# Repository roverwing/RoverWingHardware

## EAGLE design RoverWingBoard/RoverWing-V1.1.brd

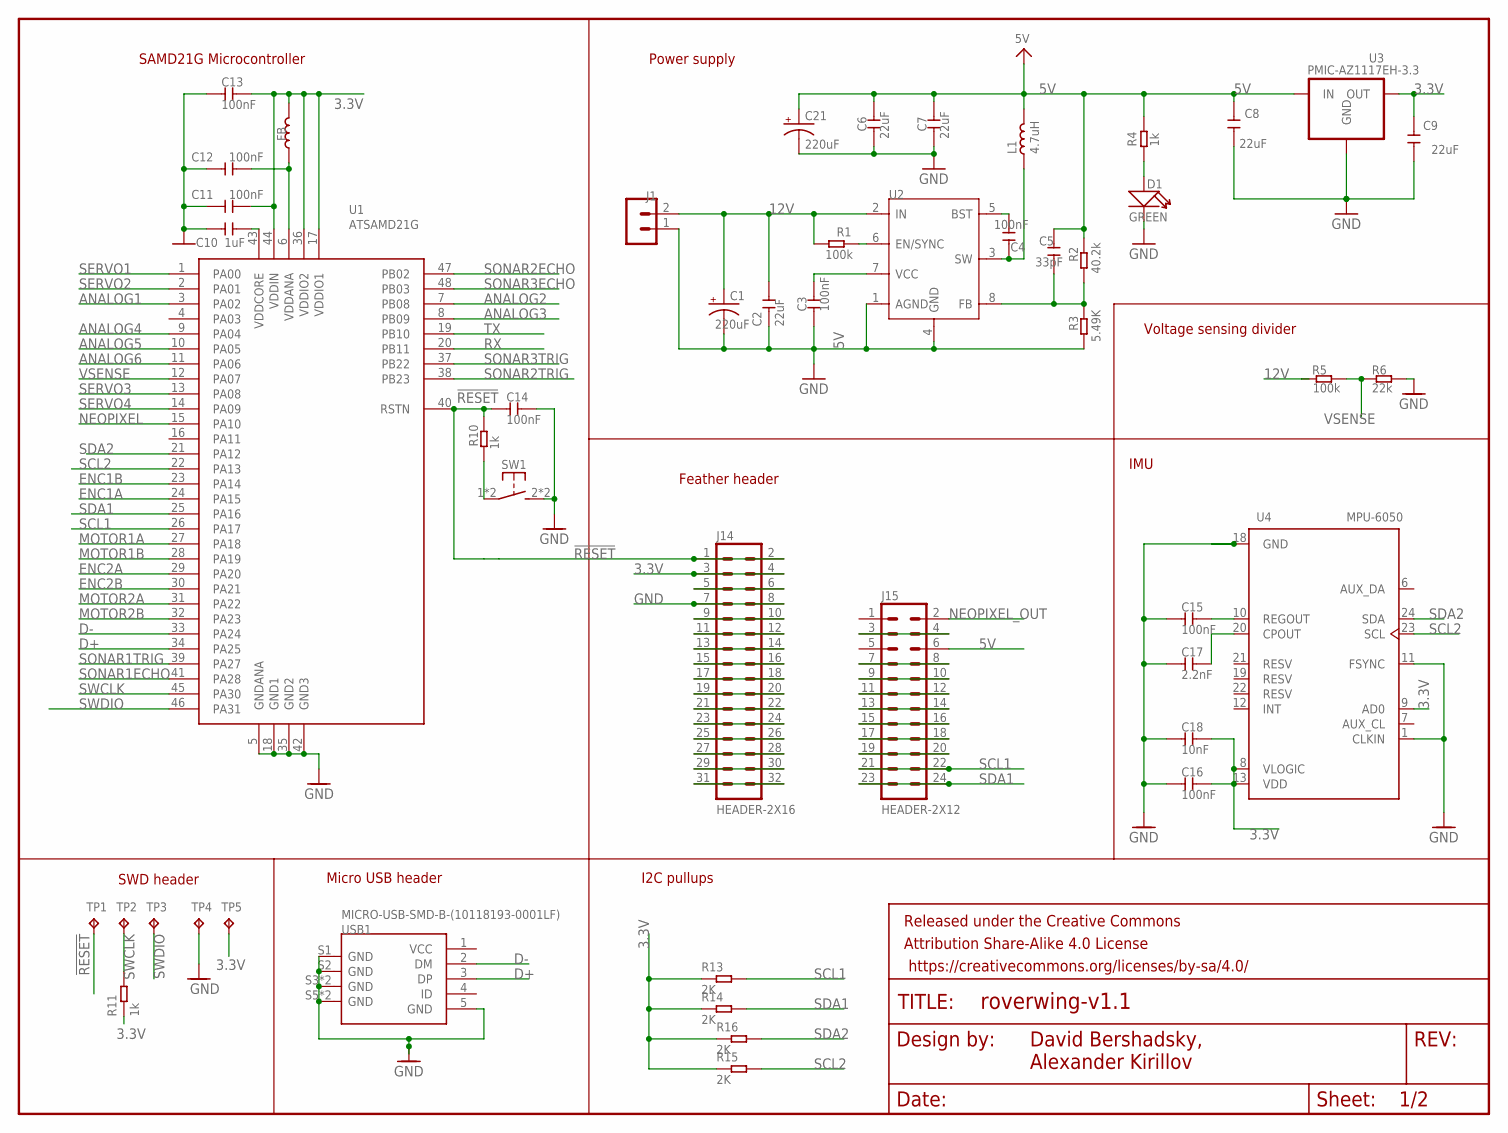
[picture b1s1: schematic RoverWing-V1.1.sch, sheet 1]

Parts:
C1: 220uF; CAP-8X10.5
C2, C6, C7, C8, C9: 22uF; 0805
C3, C4, C11, C12, C13, C14, C15, C16: 100nF; 0805
C5: 33pF; 0805
C10: 1uF; 0805
C17: 2.2nF; 0805
C18: 10nF; 0805
C21: 220uF; CAP-6.3X5.4
D1: GREEN; LED-0805
FB: 330R-1500MA; 0805
FRAME2: FRAME-LETTERNO_PACKAGE; DUMMY
J1: HEADER-VH; B2P-VH
J14: HEADER-2X16; 2X16
J15: HEADER-2X12; 2X12
L1: 4.7uH; IND_TDK_7.1X6.5
R1, R5: 100k; 0805
R2: 40.2k; 0805
R3: 5.49K; 0805
R4, R10, R11: 1k; 0805
R6: 22k; 0805
R13, R14, R15, R16: 2K; R0603
SW1: SW-TACTILE-4.5X4.5_SMD; TL3305
TP1, TP2, TP3, TP4, TP5: TPTP15R; TP15R
U1: ATSAMD21G; TQFP-48-EDITED
U2: MP2225; SOT-23-8
U3: PMIC-AZ1117EH-3.3; SOT223
U4: MPU-6050; QFN50P400X400X95-24N
USB1: MICRO-USB-SMD-B-(10118193-0001LF); MICRO-USB5+6P-SMD-0.65-B

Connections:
3.3V: C9.2, C11.2, C13.2, C16.2, C18.2, FB.2, J14.3, J14.4, R11.1, R13.1, R14.1, R15.1, R16.1, TP5.TP, U1.17 (VDDIO1), U1.36 (VDDIO2), U1.44 (VDDIN), U3.2 (OUT), U3.4 (OUT), U4.8 (VLOGIC), U4.9 (AD0), U4.13 (VDD); also elsewhere on the board
5V: C5.2, C6.2, C7.2, C8.2, C21.+, J15.6, L1.2, R2.1, R4.2, U3.3 (IN); also elsewhere on the board
12V: C1.+, C2.2, J1.2, R1.2, R5.2, U2.2 (IN); also elsewhere on the board
!RESET: C14.1, J14.1, J14.2, R10.2, TP1.TP, U1.40 (RSTN)
ANALOG1: U1.3 (PA02); also elsewhere on the board
ANALOG2: U1.7 (PB08); also elsewhere on the board
ANALOG3: U1.8 (PB09); also elsewhere on the board
ANALOG4: U1.9 (PA04); also elsewhere on the board
ANALOG5: U1.10 (PA05); also elsewhere on the board
ANALOG6: U1.11 (PA06); also elsewhere on the board
BST: C4.1, U2.5 (BST)
D+: U1.34 (PA25), USB1.3 (DP)
D-: U1.33 (PA24), USB1.2 (DM)
ENC1A: U1.24 (PA15); also elsewhere on the board
ENC1B: U1.23 (PA14); also elsewhere on the board
ENC2A: U1.29 (PA20); also elsewhere on the board
ENC2B: U1.30 (PA21); also elsewhere on the board
FB: C5.1, R2.2, R3.1, U2.8 (FB)
GND: C1.-, C2.1, C3.1, C6.1, C7.1, C8.1, C9.1, C10.1, C11.1, C12.1, C13.1, C14.2, C15.1, C16.1, C17.1, C18.1, C21.-, D1.-, J1.1, J14.7, J14.8, R3.2, R6.2, SW1.2 (S1), SW1.3 (S1), TP4.TP, U1.5 (GNDANA), U1.18 (GND1), U1.35 (GND2), U1.42 (GND3), U2.1 (AGND), U2.4 (GND), U3.1 (GND), U4.1 (CLKIN), U4.11 (FSYNC), U4.18 (GND), USB1.5 (GND), USB1.S1 (GND), USB1.S2 (GND), USB1.S3 (GND), USB1.S4 (GND), USB1.S5 (GND), USB1.S6 (GND); also elsewhere on the board
MOTOR1A: U1.27 (PA18); also elsewhere on the board
MOTOR1B: U1.28 (PA19); also elsewhere on the board
MOTOR2A: U1.31 (PA22); also elsewhere on the board
MOTOR2B: U1.32 (PA23); also elsewhere on the board
unnamed: C17.2, U4.20 (CPOUT)
unnamed: J15.3, J15.4
unnamed: C15.2, U4.10 (REGOUT)
unnamed: J15.7, J15.8
unnamed: R10.1, SW1.1, SW1.4 (P1)
unnamed: J15.9, J15.10
unnamed: C10.2, U1.43 (VDDCORE)
unnamed: J15.11, J15.12
unnamed: D1.+, R4.1
unnamed: J15.15, J15.16
unnamed: J15.13, J15.14
unnamed: R1.1, U2.6 (EN/SYNC)
unnamed: C3.2, U2.7 (VCC)
unnamed: J14.5, J14.6
unnamed: J15.17, J15.18
unnamed: J15.19, J15.20
unnamed: J14.9, J14.10
unnamed: J14.11, J14.12
unnamed: J14.13, J14.14
unnamed: J14.15, J14.16
unnamed: J14.17, J14.18
unnamed: J14.19, J14.20
unnamed: J14.21, J14.22
unnamed: J14.23, J14.24
unnamed: J14.25, J14.26
unnamed: J14.27, J14.28
unnamed: J14.29, J14.30
unnamed: J14.31, J14.32
NEOPIXEL: U1.15 (PA10); also elsewhere on the board
NEOPIXEL_OUT: J15.2; also elsewhere on the board
RX: U1.20 (PB11); also elsewhere on the board
SCL1: J15.21, J15.22, R13.2, U1.26 (PA17); also elsewhere on the board
SCL2: R15.2, U1.22 (PA13), U4.23 (SCL); also elsewhere on the board
SDA1: J15.23, J15.24, R14.2, U1.25 (PA16); also elsewhere on the board
SDA2: R16.2, U1.21 (PA12), U4.24 (SDA); also elsewhere on the board
SERVO1: U1.1 (PA00); also elsewhere on the board
SERVO2: U1.2 (PA01); also elsewhere on the board
SERVO3: U1.13 (PA08); also elsewhere on the board
SERVO4: U1.14 (PA09); also elsewhere on the board
SONAR1ECHO: U1.41 (PA28); also elsewhere on the board
SONAR1TRIG: U1.39 (PA27); also elsewhere on the board
SONAR2ECHO: U1.47 (PB02); also elsewhere on the board
SONAR2TRIG: U1.38 (PB23); also elsewhere on the board
SONAR3ECHO: U1.48 (PB03); also elsewhere on the board
SONAR3TRIG: U1.37 (PB22); also elsewhere on the board
SW: C4.2, L1.1, U2.3 (SW)
SWCLK: R11.2, TP2.TP, U1.45 (PA30)
SWDIO: TP3.TP, U1.46 (PA31)
TX: U1.19 (PB10); also elsewhere on the board
VDDANA: C12.2, FB.1, U1.6 (VDDANA)
VSENSE: R5.1, R6.1, U1.12 (PA07)

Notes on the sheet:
SWD header
David Bershadsky, Alexander Kirillov
SAMD21G Microcontroller
Micro USB header
Power supply
Feather header
IMU
Voltage sensing divider
I2C pullups

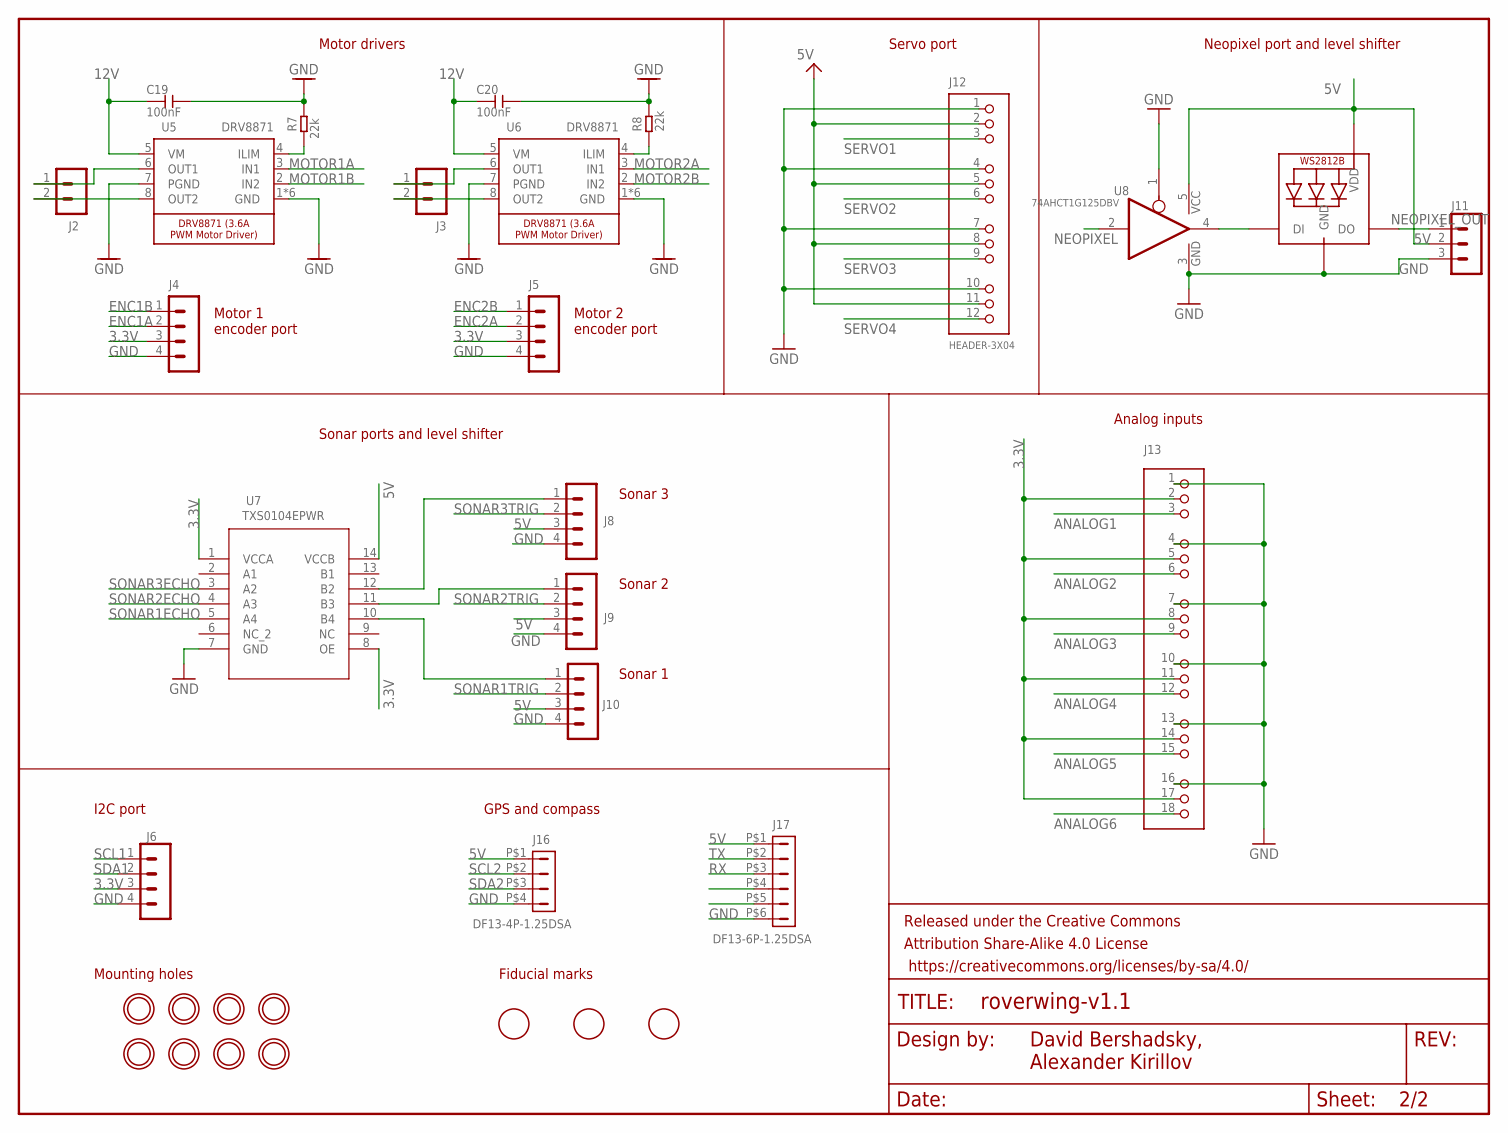
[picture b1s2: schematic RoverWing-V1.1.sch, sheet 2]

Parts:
C19, C20: 100nF; 0805
D2: WS2812B3535; LED3535
FRAME1: FRAME-LETTERNO_PACKAGE; DUMMY
J2, J3: HEADER-VH; B2P-VH
J4, J5, J6, J8, J9, J10: HEADER-PH-4P; B4B-PH-K
J11: HEADER-PH-3P; B3B-PH-K
J12: HEADER-3X04; 3X04
J13: HEADER-3X06"; 3X06
J16: DF13-4P-1.25DSA
J17: DF13-6P-1.25DSA
R7, R8: 22k; 0805
U5, U6: DRV8871; HSOP8
U7: TXS0104EPWR; PW14
U8: 74AHCT1G125DBV; SOT23-5
U$3, U$4, U$14, U$15, U$24, U$25, U$26, U$27: MOUNTINGHOLE3.0_NPH; MOUNTINGHOLE_3.0_NPH
U$11, U$13, U$17: FIDUCIAL; FIDUCIAL_1MM

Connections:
3.3V: J4.3, J5.3, J6.3, J13.2, J13.5, J13.8, J13.11, J13.14, J13.17, U7.1 (VCCA), U7.8 (OE); also elsewhere on the board
5V: D2.3 (VDD), J8.3, J9.3, J10.3, J11.2, J12.2, J12.5, J12.8, J12.11, J16.P$1 (1), J17.P$1 (1), U7.14 (VCCB), U8.5 (VCC); also elsewhere on the board
12V: C19.1, C20.1, U5.5 (VM), U6.5 (VM); also elsewhere on the board
ANALOG1: J13.3; also elsewhere on the board
ANALOG2: J13.6; also elsewhere on the board
ANALOG3: J13.9; also elsewhere on the board
ANALOG4: J13.12; also elsewhere on the board
ANALOG5: J13.15; also elsewhere on the board
ANALOG6: J13.18; also elsewhere on the board
ENC1A: J4.2; also elsewhere on the board
ENC1B: J4.1; also elsewhere on the board
ENC2A: J5.2; also elsewhere on the board
ENC2B: J5.1; also elsewhere on the board
GND: C19.2, C20.2, D2.1 (GND), J4.4, J5.4, J6.4, J8.4, J9.4, J10.4, J11.3, J12.1, J12.4, J12.7, J12.10, J13.1, J13.4, J13.7, J13.10, J13.13, J13.16, J16.P$4 (4), J17.P$6 (6), R7.2, R8.2, U5.1 (GND), U5.7 (PGND), U5.GND, U5.P$1 (GND), U5.P$2 (GND), U5.P$3 (GND), U5.P$4 (GND), U6.1 (GND), U6.7 (PGND), U6.GND, U6.P$1 (GND), U6.P$2 (GND), U6.P$3 (GND), U6.P$4 (GND), U7.7 (GND), U8.1 (OE), U8.3 (GND); also elsewhere on the board
MOTOR1A: U5.3 (IN1); also elsewhere on the board
MOTOR1B: U5.2 (IN2); also elsewhere on the board
MOTOR2A: U6.3 (IN1); also elsewhere on the board
MOTOR2B: U6.2 (IN2); also elsewhere on the board
unnamed: J3.2, U6.8 (OUT2)
unnamed: J3.1, U6.6 (OUT1)
unnamed: J2.2, U5.8 (OUT2)
unnamed: J10.1, U7.10 (B4)
unnamed: J8.1, U7.12 (B2)
unnamed: J2.1, U5.6 (OUT1)
unnamed: R7.1, U5.4 (ILIM)
unnamed: R8.1, U6.4 (ILIM)
unnamed: J9.1, U7.11 (B3)
unnamed: D2.2 (DI), U8.4 (O)
NEOPIXEL: U8.2 (I); also elsewhere on the board
NEOPIXEL_OUT: D2.4 (DO), J11.1; also elsewhere on the board
RX: J17.P$3 (3); also elsewhere on the board
SCL1: J6.1; also elsewhere on the board
SCL2: J16.P$2 (2); also elsewhere on the board
SDA1: J6.2; also elsewhere on the board
SDA2: J16.P$3 (3); also elsewhere on the board
SERVO1: J12.3; also elsewhere on the board
SERVO2: J12.6; also elsewhere on the board
SERVO3: J12.9; also elsewhere on the board
SERVO4: J12.12; also elsewhere on the board
SONAR1ECHO: U7.5 (A4); also elsewhere on the board
SONAR1TRIG: J10.2; also elsewhere on the board
SONAR2ECHO: U7.4 (A3); also elsewhere on the board
SONAR2TRIG: J9.2; also elsewhere on the board
SONAR3ECHO: U7.3 (A2); also elsewhere on the board
SONAR3TRIG: J8.2; also elsewhere on the board
TX: J17.P$2 (2); also elsewhere on the board

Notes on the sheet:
Motor drivers
Motor 2 encoder port
Motor 1 encoder port
Sonar ports and level shifter
Analog inputs
Neopixel port and level shifter
Servo port
Sonar 3
Sonar 2
Sonar 1
Mounting holes
Fiducial marks
I2C port
GPS and compass
David Bershadsky, Alexander Kirillov

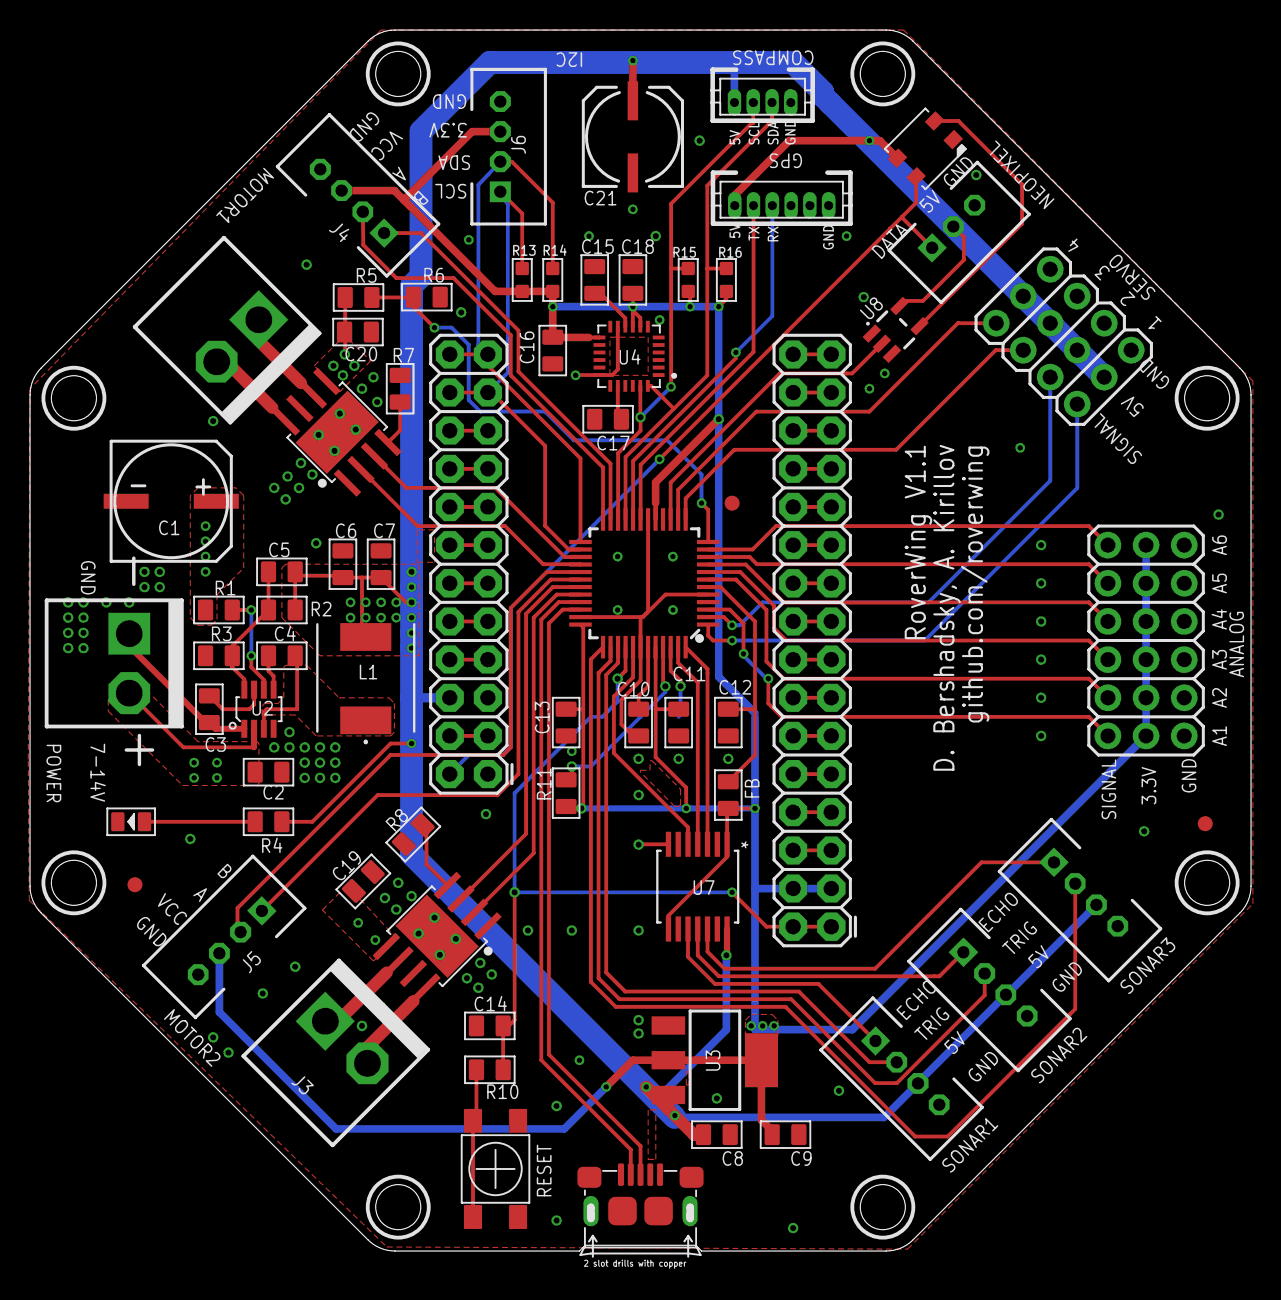
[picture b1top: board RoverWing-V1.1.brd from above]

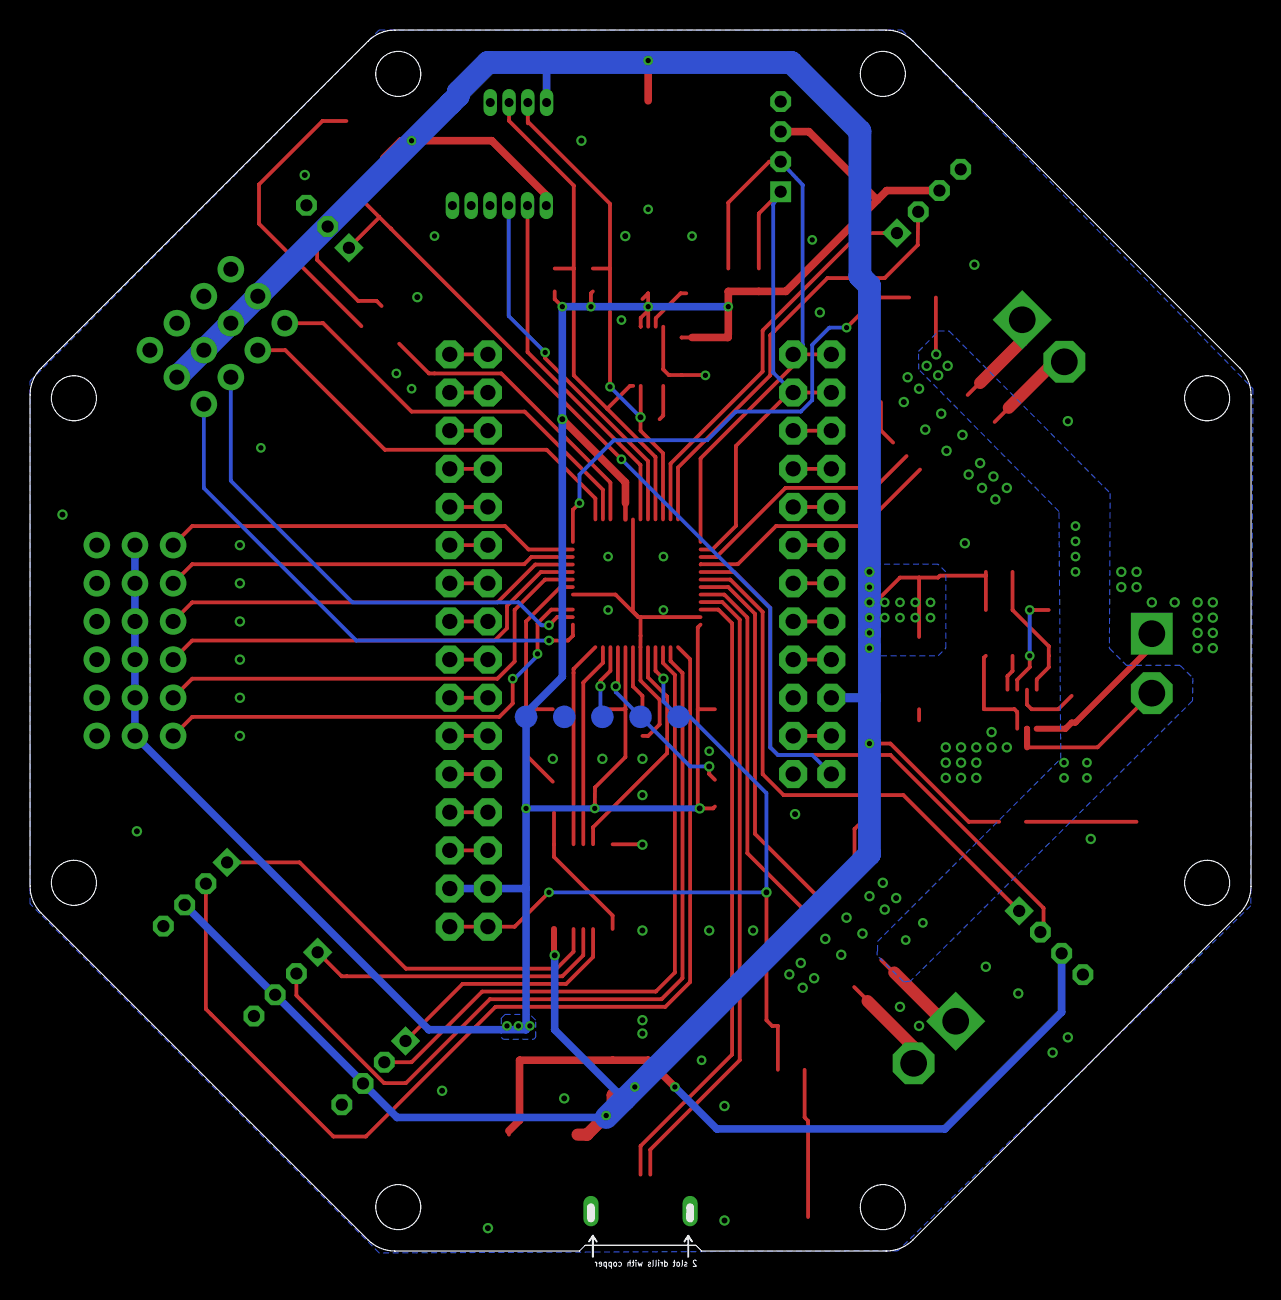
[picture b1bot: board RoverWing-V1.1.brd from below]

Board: 2 copper layers, 81.3 x 81.3 mm, 83 parts (5 on the bottom side), 84 nets.

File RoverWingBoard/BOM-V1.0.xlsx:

Parts | Qty | Value | Description | Part Num | Package | Mfg Name | Vendor | Vendor Part Num | Min quantity | Unit price | URL | Extended price
C1 | 1 | 220uF | CAP ALUM 220uF 20% 35V SMD | CK1V221MCRF10 | CAP-8X10.5 | Semtech | LCSC | C263948 | 5 | 7.2499999999999995E-2 | https://lcsc.com/product-detail/Others_Semtech-CKF1V221M0810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 | 7.2499999999999995E-2
C17 | 1 | 2.2nF | CAP CER 2.2NF 50V | C2012X7R1H222KT000N | 0805 | TDK | LCSC | C76647 | 50 | 1.52E-2 | https://lcsc.com/product-detail/Multilayer-Ceramic-Capacitor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 | 1.52E-2
C18 | 1 | 10nF | CAP CER 10NF 100V | CL21B103KCANNNC | 0805 | Samsung Electro-Mechanics | LCSC | C18741 | 50 | 1.35E-2 | https://lcsc.com/product-detail/Multilayer-Ceramic-Capacitor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 | 1.35E-2
C2, C6, C7 | 3 | 22uF | CAP CER 22uF 25V X5R | CL21A226MAQNNNE | 0805 | Samsung Electro-Mechanics | LCSC | C45783 | 5 | 0.12239999999999999 | https://lcsc.com/product-detail/Multilayer-Ceramic-Capacitor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 | 0.36719999999999997
C3, C4, C11, C12, C13, C14, C15, C16, C19, C20 | 10 | 100nF | CAP CER 0.1UF 50V | 0805B104M500NT | 0805 | Guangdong Fenghua Advanced Tech | LCSC | C286511 | 50 | 1.6899999999999998E-2 | https://lcsc.com/product-detail/Others_Guangdong-Fenghua-Adv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 | 0.16899999999999998
C5 | 1 | 33pF | CAP CER 33pF 50V | CL21C330JBANNNC | 0805 | Samsung Electro-Mechanics | LCSC | C1814 | 50 | 1.23E-2 | https://lcsc.com/product-detail/Multilayer-Ceramic-Capacitor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 | 1.23E-2
C8, C9, C10 | 3 | 1uF | CAP CER 1uF 25V | 0805B105K250AT | 0805 | Guangdong Fenghua Advanced Tech | LCSC | C111769 | 20 | 2.0299999999999999E-2 | https://lcsc.com/product-detail/Multilayer-Ceramic-Capacitor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 | 6.0899999999999996E-2
D1 | 1 | GREEN | Light Emitting Diodes (LED) Green 567.5~576.5nm 18~71mcd@20mA Top View 0805 RoHS | LTST-C170KGKT | LED-0805 | Lite-On | LCSC | C98221 | 20 | 2.76E-2 | https://lcsc.com/product-detail/Light-Emitting-Diodes-LED_LT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 | 2.76E-2
FB | 1 | 330R-1500MA | FERRITE BEAD 330 OHM 0805 1LN | BLM21PG331SN1D | 0805 | Murata Electronics | LCSC | C74764 | 20 | 3.5099999999999999E-2 | https://lcsc.com/product-detail/Ferrite-Beads-And-Chips_muRa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 | 3.5099999999999999E-2
J1, J2, J3 | 3 | HEADER-VH | CONN HEADER VH TOP 2POS 3.96MM | B2P-VH(LF)(SN) | B2P-VH | JST Sales America | LCSC | C160315 | 5 | 6.6799999999999998E-2 | * | 0.20039999999999999
J11 | 1 | HEADER-PH-3P | CONN HEADER PH TOP 3POS 2MM | B3B-PH-K-S(LF)(SN) | B3B-PH-K | JST Sales America | LCSC | C131339 | 5 | 9.9699999999999997E-2 | https://lcsc.com/product-detail/PCB-Connectors-Headers-Male-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 | 9.9699999999999997E-2
J12 | 1 | HEADER-3X04 | * | * | 3X04 | * | * | * | * | * | *
J13 | 1 | HEADER-3X06 | * | * | 3X06 | * | * | * | * | * | *
J14 | 1 | HEADER-2X16 | FEMALE HEADER 2*16 2.54MM | DS1023-2*16SF11 | 2X16 | CONNFLY Elec | LCSC | C132130 | 1 | 0.1454 | https://lcsc.com/product-detail/Female-Header_DS1023-2-16SF1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 | 0.1454
J15 | 1 | HEADER-2X12 | FEMALE HEADER 2*12 2.54MM | DS1023-2*12SF11 | 2X12 | CONNFLY Elec | LCSC | C92265 | 1 | 0.1201 | https://lcsc.com/product-detail/Female-Header_2-54Female-hea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 | 0.1201
J16 | 1 | DF13-4P-1.25DSA | CONN HEADER DF13 4POS 1.25MM | DF13-4P-1.25DSA | DF13-4P-1.25DSA | Hirose | LCSC | C202091 | 1 | 0.26550000000000001 | https://lcsc.com/product-detail/Connectors_Hirose_DF13-4P-1-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 | 0.26550000000000001
J17 | 1 | DF13-6P-1.25DSA | CONN HEADER DF13 6POS 1.25MM | DF13-6P-1.25DSA | DF13-6P-1.25DSA | Hirose | Digikey | H2195-ND | 1 | 0.33 | https://www.digikey.com/product-detail/en/hirose-electric-co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 | 0.33
J4, J5, J6, J7, J8, J9, J10 | 7 | HEADER-PH-4P | CONN HEADER PH TOP 4POS 2MM | B4B-PH-K-S(LF)(SN) | B4B-PH-K | JST Sales America | LCSC | C160257 | 10 | 5.91E-2 | https://lcsc.com/product-detail/Wire-To-Board-Wire-To-Wire-C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 | 0.41370000000000001
L1 | 1 | 4.7uH | Power Inductors 4.7uH Â±20% 5.6A | SPM6530T-4R7M | IND_TDK_7.1X6.5 | TDK | LCSC | C76857 | 10 | 0.1082 | https://lcsc.com/product-detail/Power-Inductors_TDK_SPM6530T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 | 0.1082
LED1 | 1 | WS2812B3535 | SMART LED, 3.5MM SMD | WS2812B-3535 | LED3535 | Worldsemi | LCSC | C114583 | 5 | 0.1145 | https://lcsc.com/product-detail/Light-Emitting-Diodes-LED_35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 | 0.1145
R1, R5 | 2 | 100k | RES SMD 100K OHM 1% | RC0805FR-07100KL | 0805 | YAGEO | LCSC | C96346 | 50 | 5.4000000000000003E-3 | https://lcsc.com/product-detail/Chip-Resistor-Surface-Mount_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 | 1.0800000000000001E-2
R11 | 1 | 2.7k*4 | Resistor Networks & Arrays 2.7KOhms Â±5% 1/16W 0603_x4 | RTA03-4D272JTP | 0603*4 | RALEC | LCSC | C102660 | 50 | 8.6999999999999994E-3 | https://lcsc.com/product-detail/Resistor-Networks-Arrays_2-7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 | 8.6999999999999994E-3
R2 | 1 | 40.2k | RES SMD 40.2KOhms ±1% 1/8W 0805 RoHS | RC0805FR-0740K2L | 0805 | YAGEO | LCSC | C273827 | 100 | 2.3999999999999998E-3 | https://lcsc.com/product-detail/Others_YAGEO-RC0805FR-0740K2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 | 2.3999999999999998E-3
R3 | 1 | 5.49 | RES SMD 5.49KOhms ±1% 1/8W 0805 RoHS | RC0805FR-075K49L | 0805 | YAGEO | LCSC | C273977 | 50 | 3.8E-3 | https://lcsc.com/product-detail/Others_YAGEO-RC0805FR-075K49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 | 3.8E-3
R4, R10, R109 | 3 | 1k | RES SMD 1K OHMs Â±5% 1/8W | RC0805JR-071KL | 0805 | YAGEO | LCSC | C100046 | 50 | 2.7000000000000001E-3 | https://lcsc.com/product-detail/Chip-Resistor-Surface-Mount_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 | 8.0999999999999996E-3
R6, R7, R8 | 3 | 22k | RES SMD 22KOhms Â±1% | RC0805FR-0722KL | 0805 | YAGEO | LCSC | C114565 | 50 | 4.3E-3 | https://lcsc.com/product-detail/Chip-Resistor-Surface-Mount_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 | 1.29E-2
SW1 | 1 | SW-TACTILE-4.5X4.5_SMD | Tactile Switches SPST 4.50mm x 4.50mm 0.90mm 50mA @ 12VDC SMD RoHS | TSA453G38-250 | TL3305 | BRIGHT | LCSC | C294494 | 20 | 2.5399999999999999E-2 | https://lcsc.com/product-detail/Tactile-Switches_BRIGHT-TSA4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 | 2.5399999999999999E-2
U1 | 1 | ATSAMD21G | IC MCU 32BIT 256KB FLASH 48TQFP | ATSAMD21G18A-AU | TQFP-48-EDITED | Microchip Technology | Digikey | ATSAMD21G18A-AU-ND | 1 | 3.22 | https://www.digikey.com/product-detail/en/microchip-technolo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 | 3.22
U2 | 1 | PMIC-MP2225 | DC-DC Converters Step-Down Adjustable 1 4.5V 18V 0.6V 17V 5A TSOT-23-8Â | MP2225GJ-Z | SOT-23-8 | Monolithic Power Systems | LCSC | C133066 | 10 | 0.32140000000000002 | https://lcsc.com/product-detail/DC-DC-Converters_MPS_MP2225G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 | 0.32140000000000002
U3 | 1 | AZ1117EH-3.3 | Low Dropout Regulators(LDO) Positive Fixed 1.3V @ 1A 13V 3.3V 1AÂ | AZ1117EH-3.3TRG1 | SOT223 | Diodes Inc | LCSC | C108494 | 5 | 8.1299999999999997E-2 | https://lcsc.com/product-detail/Low-Dropout-Regulators-LDO_D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 | 8.1299999999999997E-2
U4 | 1 | MPU-6050 | IMU ACCEL/GYRO 3-AXIS I2C 24QFN | MPU-6050 | QFN50P400X400X95-24N | TDK InvenSense | LCSC | C24112 | 1 | 2.8835000000000002 | https://lcsc.com/product-detail/Attitude-Sensors_TDK-InvenSe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 | 2.8835000000000002
U5, U6 | 2 | DRV8871 | Motor Drivers SO-8 RoHS | DRV8871DDAR | HSOP8 | Texas Instruments | LCSC | C75864 | 1 | 1.7250000000000001 | https://lcsc.com/product-detail/Motor-Drivers_TI_DRV8871DDAR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 | 3.45
U7 | 1 | TXS0104EPWR | Level Translators, Shifters TSSOP-14 RoHS | TXS0104EPWR | PW14 | Texas Instruments | LCSC | C44955 | 1 | 0.69340000000000002 | https://lcsc.com/product-detail/Interface-ICs_TI_TXS0104EPWR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 | 0.69340000000000002
U8 | 1 | 74AHCT1G125DBV | 74 Series Buffer, Non-Inverting 4.5V ~ 5.5V SOT-23-5 RoHS | SN74AHCT1G125DBVR | SOT23-5 | Texas Instruments | LCSC | C7484 | 5 | 0.12809999999999999 | https://lcsc.com/product-detail/74-Series_TI_SN74AHCT1G125DB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 | 0.12809999999999999
USB1 | 1 | MICRO-USB-SMD-B-(10118193-0001LF) | CONN USB MICRO B RECPT SMT R/A | 10118193-0001LF | MICRO-USB5+6P-SMD-0.65-B | Amphenol ICC | LCSC | C132562 | 1 | 0.24 | https://lcsc.com/product-detail/USB-Connectors_Amphenol_1011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 | 0.24
Total price

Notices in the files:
parts and their libraries:
RoverWing: Released under the Creative Commons
RoverWing: https://creativecommons.org/licenses/by-sa/4.0
